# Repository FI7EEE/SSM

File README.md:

# 
# SSM (Smart Space Monitoring)
# Deskripsi Proyek: Smart Space Management
Smart Space Management adalah sebuah sistem inovatif yang dirancang untuk memudahkan proses pemesanan serta monitoring penggunaan ruangan secara real-time. Proyek ini bertujuan untuk meningkatkan efisiensi pemanfaatan ruang, khususnya di lingkungan perkantoran, kampus, atau fasilitas umum lainnya.
Sistem ini memanfaatkan antarmuka pengguna yang dirancang melalui Figma, yang memberikan tampilan pemesanan ruangan yang intuitif dan mudah digunakan. Pengguna dapat melihat ketersediaan ruangan, melakukan reservasi, serta memantau status ruangan secara langsung melalui dashboard yang telah disiapkan.

Untuk mendukung fungsionalitas monitoring, sistem ini dikombinasikan dengan beberapa sensor sebagai pengganti kamera, guna menjaga privasi namun tetap menyediakan informasi yang akurat:
DHT22: Sensor suhu dan kelembapan yang berguna untuk mengetahui kondisi lingkungan dalam ruangan secara real-time.
RCWL-0516: Sensor pendeteksi gerakan berbasis gelombang mikro yang berfungsi untuk mendeteksi keberadaan orang dalam ruangan tanpa menggunakan kamera.
Toggle Switch: Digunakan sebagai indikator manual kehadiran atau aktivitas di dalam ruangan, sekaligus sebagai alternatif input kondisi ruangan.

Dengan integrasi antara antarmuka digital dan sensor fisik ini, Smart Space Management menawarkan solusi yang efisien, ramah privasi, dan mudah diimplementasikan untuk manajemen ruang yang lebih cerdas dan terorganisir.

# Tujuan Proyek:
Merancang dan mengimplementasikan sistem manajemen ruang berbasis antarmuka digital (Figma) yang terintegrasi dengan sensor DHT22, RCWL-0516, dan toggle switch untuk memungkinkan proses pemesanan, pemantauan kondisi lingkungan, serta deteksi keberadaan pengguna secara real-time tanpa penggunaan kamera, guna meningkatkan efisiensi pemanfaatan ruang dan menjaga privasi.
### Support BY :
>- Dosen Pengampu : Akhmad Hendriawan ST., MT. (NIP.197501272002121003)<br>
>- Mata kuliah : Workshop Mikrokontroller<br>
>- Program Studi : D3 Teknik Elektronika<br>
>- Politeknik Elektronika Negeri Surabaya<br>
# Anggota Tim
# 
|      NRP      |        Nama       |        Jobdesk        |                    Akun                  |
| :-----------: |:----------------: | :-------------------: | :---------------------------------------:|
| 2123500009    | Adrian Iqbal R    | Software              | [Adrian](https://github.com/AdrianIqbalR)
| 2123500016    | Royyan Firdaus M  | Hardware Specialist   | [Royyan](https://github.com/nataratungga)
| 2123500026    | Aditya Wahyu W    | 3D Design          | [Adit](https://github.com/AdityaWahyuW)
| 2123500029    | Khrisna P.Y       | Project Manager       | [Khrisna](https://github.com/Khrisnapy)
| 2123500033    | Bintang Firgi     | UI UX Design           | [Bintang](https://github.com/FI7EEE)
# Komponen 
>- RCWL 0516 / Sensor radar → untuk deteksi keberadaan orang.
>- DHT22 / Sensor suhu  → untuk mengukur suhu dan kelembaban udara.
>- Switch (Pengganti Kamera) → untuk deteksi keberadaan orang dengan logic 0/1
>- Arduino nano / NodeMCU → mikrokontroler pengolah data sensor.
>- UART / MQTT / WiFi → komunikasi data antar perangkat.
>- Database (Firebase / MySQL) → menyimpan status ruangan dan data reservasi.
>- Web / Mobile App → untuk tampilan UI pengguna dan admin.
# Hardware
# 
# 
# 
# Desain 3D
# <center><br>
# <center>
# Desain 3D case
# <center><br>
# <center><br>
# <center>
# Cetak 3D
# <center>
# Blok Diagram
# <center>
-Trigger Awal: Customer melakukan booking melalui sistem.
-Sistem Aktif: Arduino Nano mulai membaca input dari sensor radar dan DHT-22.
-Pengiriman Data: Data hanya dikirim jika ada pergerakan terdeteksi.
-Interface Website: Menyajikan hasil monitoring secara real-time.
# Diagram Arsitektur Sistem
# <center>
# UI/UX
### WebSite
[https://github.com/user-attachments/assets/d8675519-fc17-4f6d-9039-62dc81f8e6db](https://github.com/user-attachments/assets/98683b24-d88b-4f35-aa60-ffe053077857)
# Simulasi Program
https://github.com/user-attachments/assets/06786ef0-06cf-4453-9f95-b31134c98d04
# Iklan Produk
https://github.com/user-attachments/assets/8dcf32cc-ab39-48ea-9cd7-9ef755d4262f
##
Pada sistem SSM ini menggunakan 2 input sensor dan 1 kamera untuk mengetahui status/kondisi ruangan sedang terpakai maupun ruangan sedang kosong. Disini kami menggunakan sensor radar RCWL 0516 sebagai sensor pendeteksi gerakan, sensor DHT 22 sebagai monitoring suhu ruangan, dan switch disini sebagai pengganti kamera. Apabila switch bernilai logic 1 (true) maka diibaratkan sebagai kamera yang mendeteksi keberadaan orang/ruangan sedang terpakai, sebaliknya apabila switch bernilai logic 0 (false) diibaratkan ruangan sedang kosong/tidak terpakai. Lalu output/hasil pembacaan data oleh sensor dan switch tadi dikirim ke database dan akan ditampilkan pada web admin pengelola ruangan. Dari data data tersebut admin bisa mengetahui status ketersediaan ruangan.
# Panduan Penggunaan
1. Pastikan perangkat sudah terkoneksi dengan daya.
2. Akses web SSM pada Link berikut : https://smartspacemanagement-ba2ef.web.app/
3. Login sebagai user jika ingin reservasi ruangan.
4. Pada tampilan web user terdapat daftar ruangan yang tersedia ataupun sedang digunakan. Pada tampilan user juga terdapat fitur untuk reservasi yang akan terhubung ke web admin.
5. Jika ingin reservasi ruangan, kirim data ruangan dan jam yang dipilih, maka data akan terkirim ke admin dan menunggu persetujuan.
6. Login sebagai admin jika ingin mengakses web admin guna monitoring ruangan dan sistem.
7. Admin dapat melihat data ruangan yang tersedia dan yang sedang digunakan, admin juga dapat menyetujui maupun menolak reservasi dari user.
8. Jika permintaan di setujui maka user berhasil reservasi ruangan.

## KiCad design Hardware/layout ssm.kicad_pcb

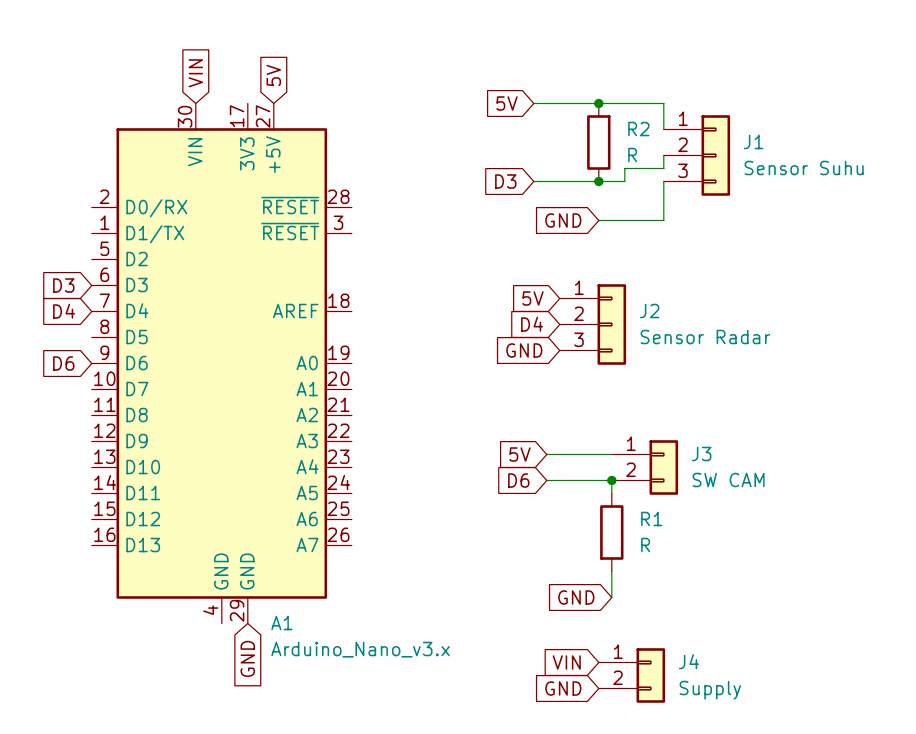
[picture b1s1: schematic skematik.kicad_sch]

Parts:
A1: Arduino_Nano_v3.x; Arduino_Nano
J1: Sensor Suhu; PinHeader_1x03_P2.54mm_Vertical
J2: Sensor Radar; PinHeader_1x03_P2.54mm_Vertical
J3: SW CAM; PinHeader_1x02_P2.54mm_Vertical
J4: Supply; PinHeader_1x02_P2.54mm_Vertical
R1, R2: R; R_1206_3216Metric_Pad1.30x1.75mm_HandSolder

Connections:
5V: A1.27 (+5V), J1.1, J2.1, J3.1, R2.2
D3: A1.6 (D3), J1.2, R2.1
D4: A1.7 (D4), J2.2
D6: A1.9 (D6), J3.2, R1.1
GND: A1.29 (GND), J1.3, J2.3, J4.2, R1.2
VIN: A1.30 (VIN), J4.1

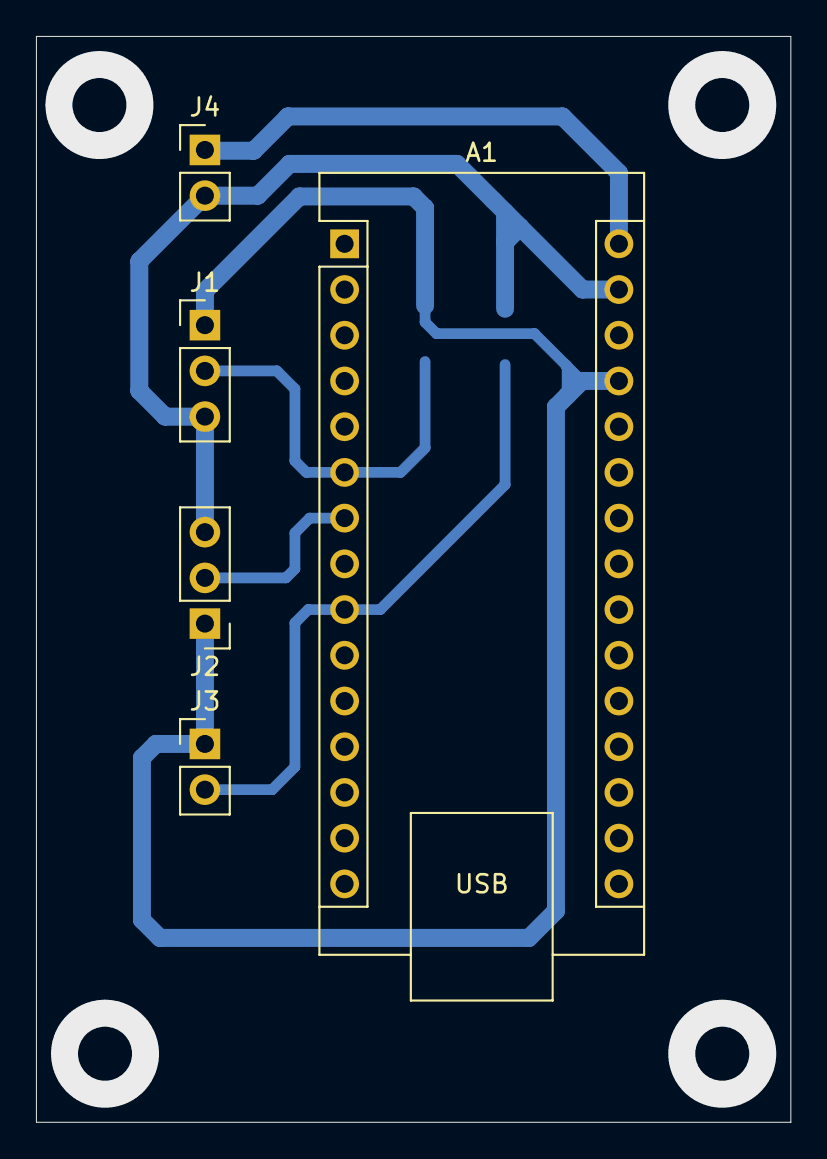
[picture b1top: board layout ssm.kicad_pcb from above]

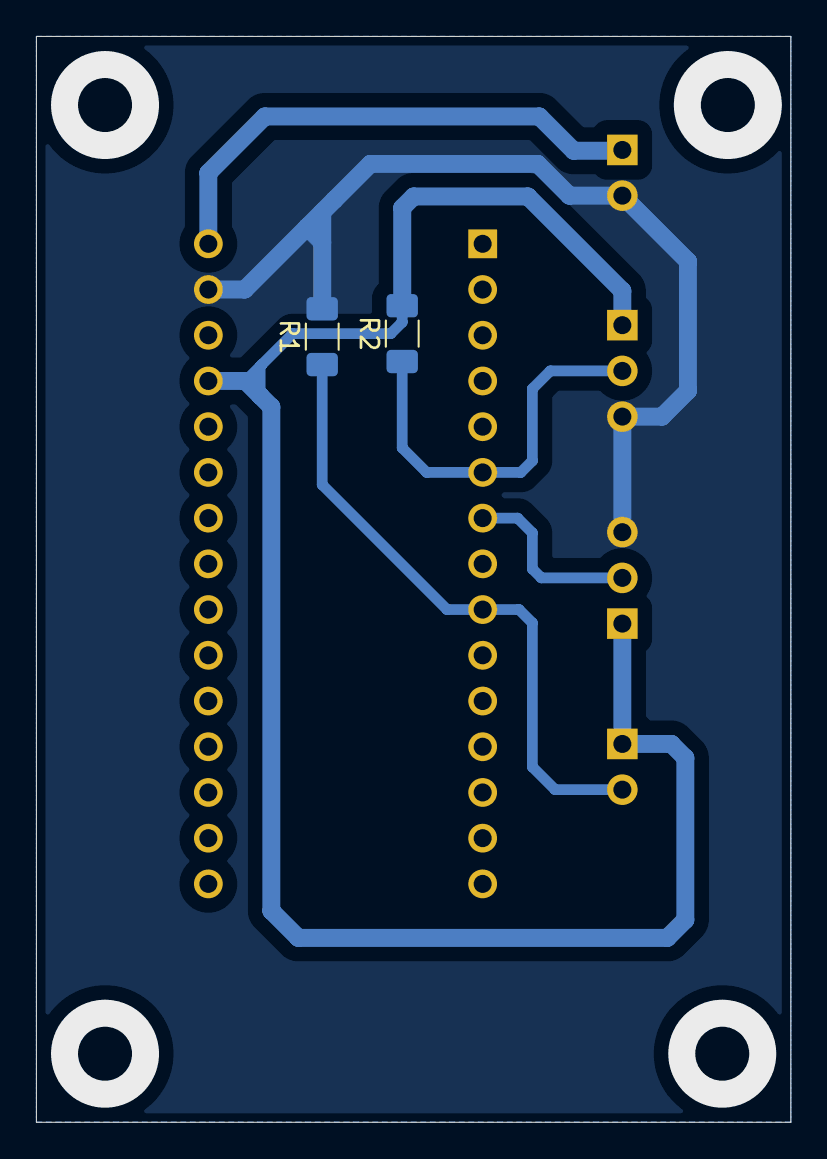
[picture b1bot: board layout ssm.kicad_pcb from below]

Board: 2 copper layers, 41.9 x 60.3 mm, 7 parts (2 on the bottom side), 6 nets.

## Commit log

2025-04-18 Create Desain 3D
2025-04-20 Create LOGo
2025-04-24 Create readme.md
    Slide Presentasi Smart Space Management
2025-04-24 Add files via upload
    beberapa komponen yang dibutuhkan untuk project SSM
2025-04-24 Create Week 1
2025-04-24 Rename main.md to Readme.md
2025-04-25 menambahkan foto
2025-04-25 upadte deskripsi tim
    nama nrp dan jobdesk
2025-04-27 update landing page logo
    fix design landing page
2025-04-27 update all lanpag
    tampilan awal
2025-04-27 Update readme.md
    deskripsi tentang dashboard awal ,supaya mudah jika butuh tinggal copy paste
2025-04-27 update login/regis page
    membuat desain figma login dan registrasi
2025-04-27 Rename admin.png to user.png
2025-04-27 Update readme.md
    +login dan signup design figma
2025-04-27 Rename user.png to admin.png
2025-04-27 Rename Cuplikan layar 2025-04-24 150930.png to 3D Komponen.png
2025-04-27 Rename Cuplikan layar 2025-04-24 151003.png to 3D Komponen2.png
2025-04-27 Rename Adit.jpg to Foto Adit.jpg
2025-04-27 Update bug
    dollor
    sit
    amet
2025-04-27 Update readme.md
    update ui
2025-04-27 update file ui lpage
    dolor
    sit amet
    not404
2025-04-27 bug file
    dolor
    sit
    amet
    404not respondet
2025-04-27 update bug ,cant fixed
    Lorem ipsum dolor sit amet, consectetur adipiscing elit. Integer dui massa, feugiat eget felis nec, molestie pulvinar urna. Aliquam erat volutpat. Class aptent taciti sociosqu ad litora torquent per 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
    Nulla tincidunt risus at metus tristique auctor. Etiam posuere rutrum es
2025-04-27 Upadate Completed
    Lorem ipsum dolor sit amet, consectetur adipiscing elit. Nullam non purus commodo, sagittis est in, scelerisque lorem. Cras non varius ex. Praesent ultrices sollicitudin porttitor. Phasellus viverra 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
    Quisque viverra dignissim enim, ac sagittis massa mollis et. Curabitur tincidunt, eros vel interdum euismod, arcu odio ornare ex, eget consectetur est arcu ac lacus. Sed aliquam sapien sed ultrices t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
2025-04-27 Update 3D PLate
    Lorem ipsum dolor sit amet
2025-04-28 generate ai
    coba membuat codeneya dengan ai menggunakan anama app
2025-04-28 LandingPage Figma to Web (anima.app AI)
    mencoba menggunakan ai
2025-04-28 ai figma to code
2025-05-19 Create Blok Diagram
2025-05-25 Rename Assets/Foto TIM/Green Blue Modern Future Technology Presentation.jpg to Foto Teammates.jpg
2025-05-25 3D Tinkercad
